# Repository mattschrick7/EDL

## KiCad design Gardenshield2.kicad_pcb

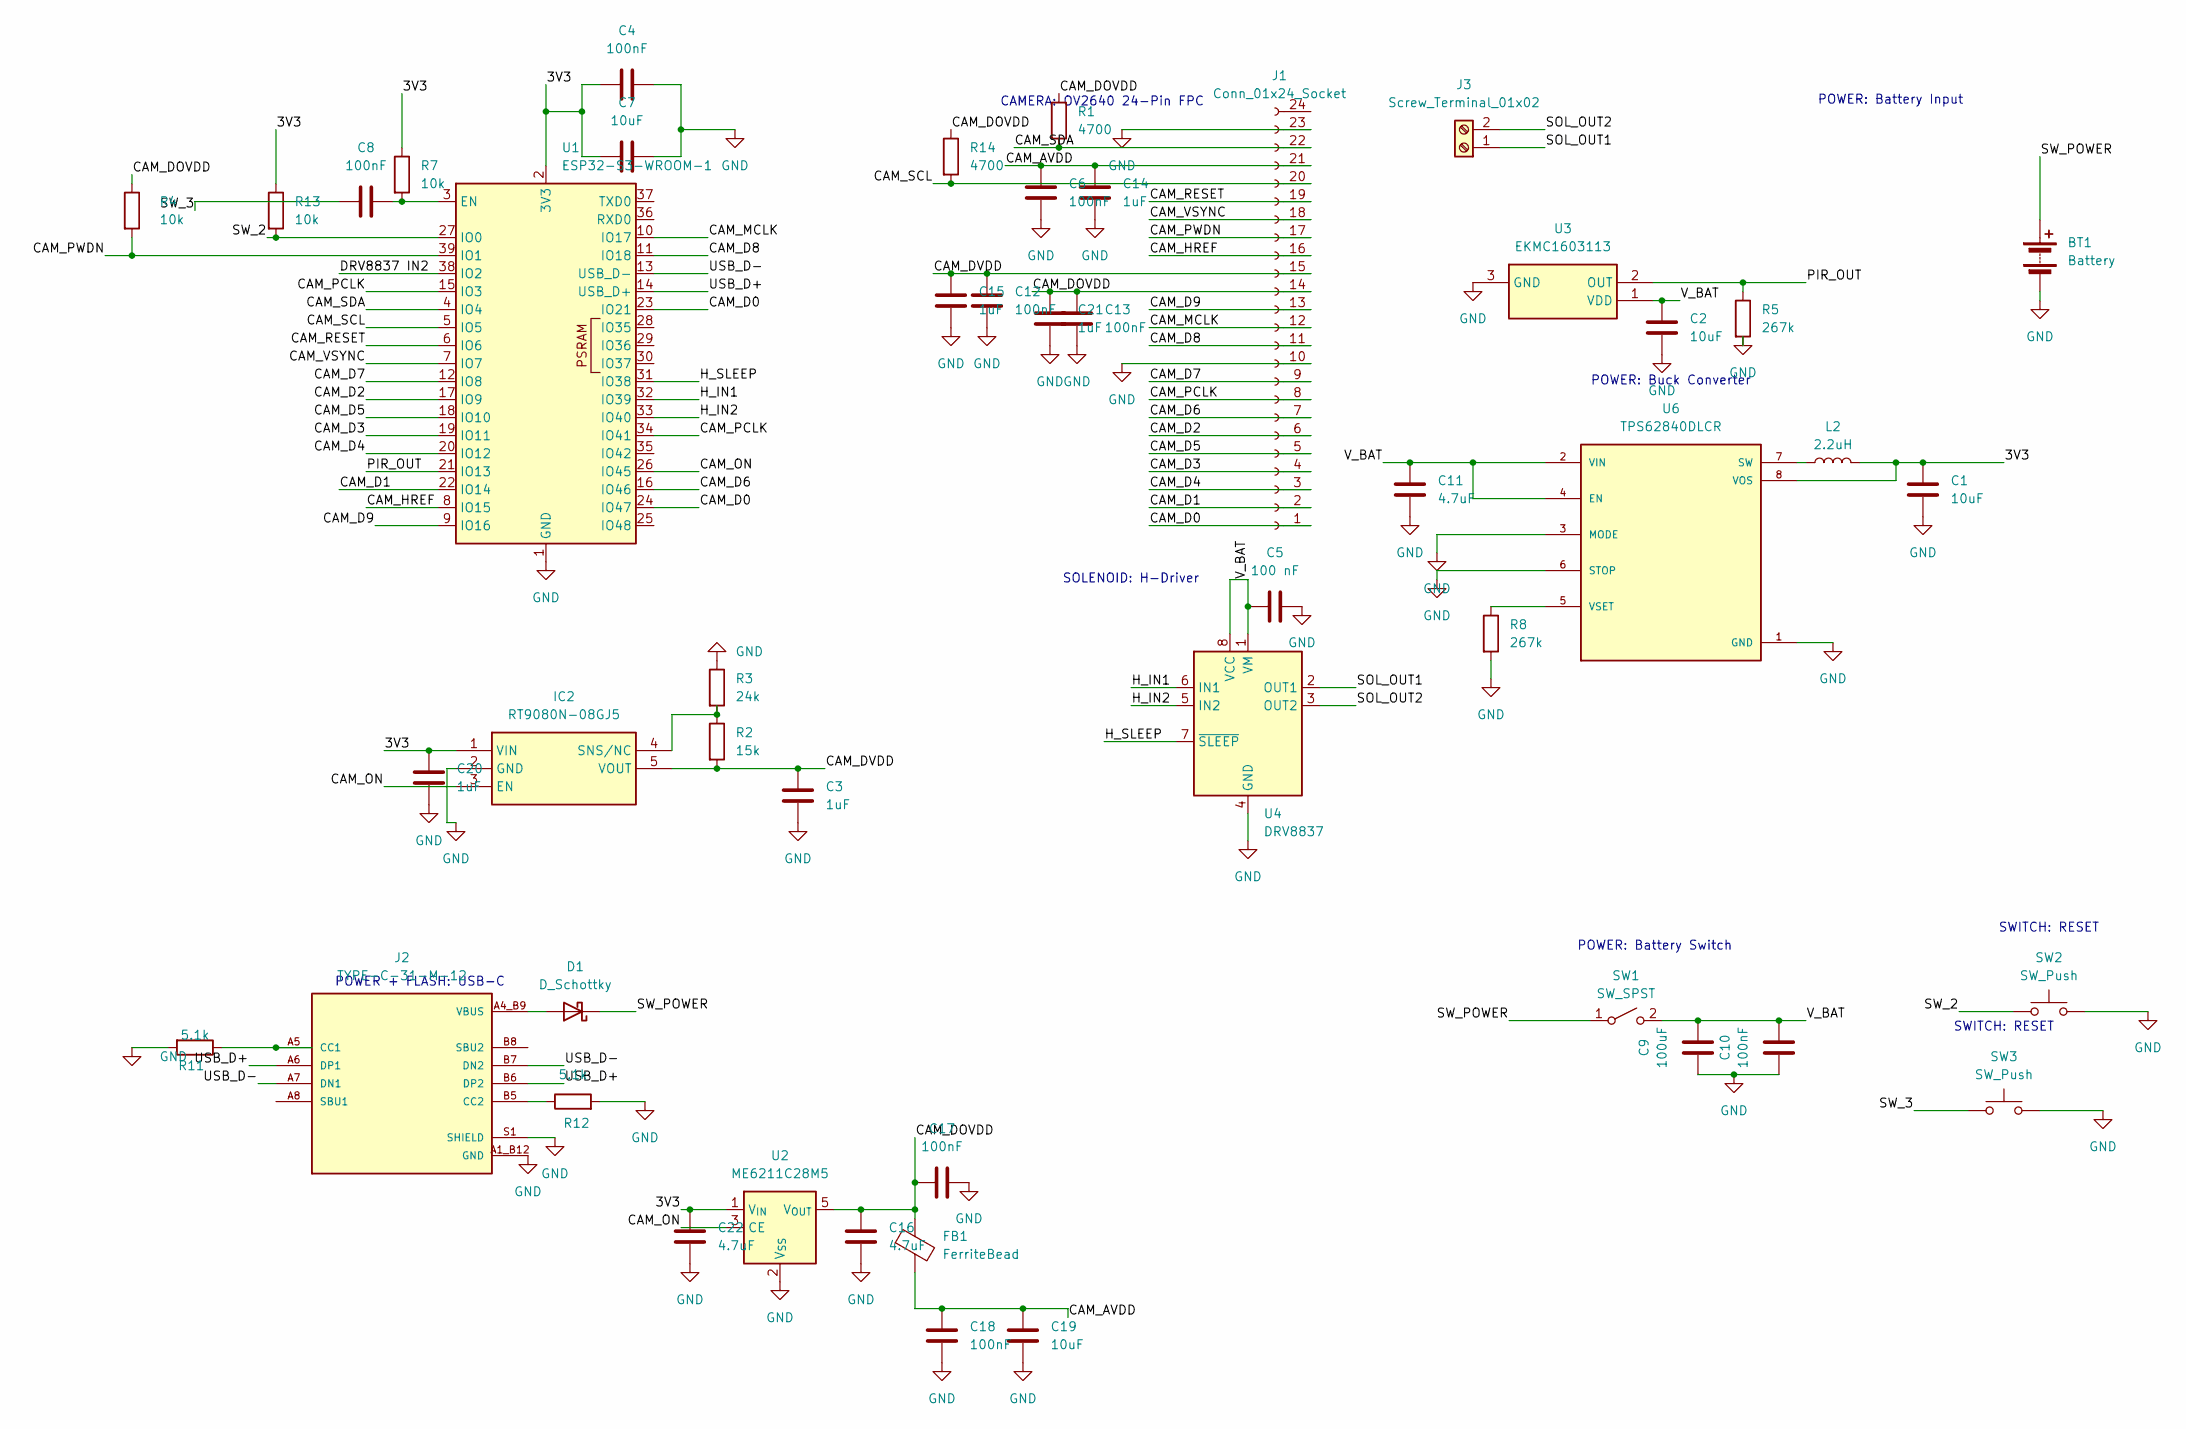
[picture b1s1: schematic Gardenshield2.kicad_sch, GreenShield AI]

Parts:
BT1: Battery; BatteryHolder_TruPower_BH-331P_3xAA
C1, C2, C7, C19: 10uF; C_0805_2012Metric
C3: 1uF; C_0402_1005Metric
C4, C6, C8, C10, C12, C13, C17, C18: 100nF; C_0603_1608Metric
C5: 100 nF; C_0603_1608Metric
C9: 100uF; CP_Elec_6.3x5.8
C11, C16, C22: 4.7uF; C_0603_1608Metric
C14, C15, C20, C21: 1uF; C_0603_1608Metric
D1: D_Schottky; D_SMA
FB1: FerriteBead; C_0805_2012Metric
IC2: RT9080N-08GJ5; SOT94P280X100-5N; Mouser Part Number 835-RT9080N-08GJ5
J1: Conn_01x24_Socket; F32R1A7H111024
J2: TYPE-C-31-M-12; HRO_TYPE-C-31-M-12; PARTREV 2020.12.08
J3: Screw_Terminal_01x02; TerminalBlock_MaiXu_MX126-5.0-02P_1x02_P5.00mm
L2: 2.2uH; L_0805_2012Metric
R1, R14: 4700; R_0603_1608Metric
R2: 15k; R_0805_2012Metric
R3: 24k; R_0805_2012Metric
R4, R7, R13: 10k; R_0603_1608Metric
R5, R8: 267k; R_0603_1608Metric
R11, R12: 5.1k; R_0603_1608Metric
SW1: SW_SPST; SW_TS-1088-AR02016
SW2, SW3: SW_Push; SW_TS-1088-AR02016
U1: ESP32-S3-WROOM-1
U2: ME6211C28M5; SOT-23-5
U3: EKMC1603113; Mouser Part Number 769-EKMC1603113
U4: DRV8837; WSON-8-1EP_2x2mm_P0.5mm_EP0.9x1.6mm
U6: TPS62840DLCR; SON50P200X150X100-8N

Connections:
/3V3: C1.1, C4.1, C7.1, C20.1, C22.1, IC2.1 (VIN), L2.2, R7.1, R13.1, U1.2 (3V3), U2.1 (V_{IN}), U6.8 (VOS)
/CAM_AVDD: C6.1, C14.1, C18.1, C19.1, FB1.2, J1.21
/CAM_D0: J1.1, U1.23 (IO21), U1.24 (IO47)
/CAM_D1: J1.2, U1.22 (IO14)
/CAM_D2: J1.6, U1.17 (IO9)
/CAM_D3: J1.4, U1.19 (IO11)
/CAM_D4: J1.3, U1.20 (IO12)
/CAM_D5: J1.5, U1.18 (IO10)
/CAM_D6: J1.7, U1.16 (IO46)
/CAM_D7: J1.9, U1.12 (IO8)
/CAM_D8: J1.11, U1.11 (IO18)
/CAM_D9: J1.13, U1.9 (IO16)
/CAM_DOVDD: C13.1, C16.1, C17.1, C21.1, FB1.1, J1.14, R1.1, R4.1, R14.1, U2.5 (V_{OUT})
/CAM_DVDD: C3.1, C12.1, C15.1, IC2.5 (VOUT), J1.15, R2.2
/CAM_HREF: J1.16, U1.8 (IO15)
/CAM_MCLK: J1.12, U1.10 (IO17)
/CAM_ON: IC2.3 (EN), U1.26 (IO45), U2.3 (CE)
/CAM_PCLK: J1.8, U1.15 (IO3), U1.34 (IO41)
/CAM_PWDN: J1.17, R4.2, U1.39 (IO1)
/CAM_RESET: J1.19, U1.6 (IO6)
/CAM_SCL: J1.20, R14.2, U1.5 (IO5)
/CAM_SDA: J1.22, R1.2, U1.4 (IO4)
/CAM_VSYNC: J1.18, U1.7 (IO7)
/DRV8837 IN2: U1.38 (IO2)
/H_IN1: U1.32 (IO39), U4.6 (IN1)
/H_IN2: U1.33 (IO40), U4.5 (IN2)
/H_SLEEP: U1.31 (IO38), U4.7 (~SLEEP)
/PIR_OUT: R5.1, U1.21 (IO13), U3.2 (OUT)
/SOL_OUT1: J3.1, U4.2 (OUT1)
/SOL_OUT2: J3.2, U4.3 (OUT2)
/SW_2: R13.2, SW2.1, U1.27 (IO0)
/SW_3: C8.1, SW3.1
/SW_POWER: BT1.1 (+), D1.1 (K), SW1.1 (A)
/USB_D+: J2.A6 (DP1), J2.B6 (DP2), U1.14 (USB_D+)
/USB_D-: J2.A7 (DN1), J2.B7 (DN2), U1.13 (USB_D-)
/V_BAT: C2.1, C5.1, C9.2, C10.2, C11.1, SW1.2 (B), U3.1 (VDD), U4.1 (VM), U4.8 (VCC), U6.2 (VIN), U6.4 (EN)
GND: BT1.2 (-), C1.2, C2.2, C3.2, C4.2, C5.2, C6.2, C7.2, C9.1, C10.1, C11.2, C12.2, C13.2, C14.2, C15.2, C16.2, C17.2, C18.2, C19.2, C20.2, C21.2, C22.2, IC2.2 (GND), J1.10, J1.23, J2.A1_B12 (GND), J2.B1_A12 (GND), J2.S1 (SHIELD), J2.S2 (SHIELD), J2.S3 (SHIELD), J2.S4 (SHIELD), R3.1, R5.2, R8.2, R11.2, R12.2, SW2.2, SW3.2, U1.1 (GND), U1.40 (GND), U1.41 (GND), U2.2 (V_{SS}), U3.3 (GND), U4.4 (GND), U4.9 (GND), U6.1 (GND), U6.3 (MODE), U6.6 (STOP)
unnamed: IC2.4 (SNS/NC), R2.1, R3.2
unnamed: J2.A5 (CC1), R11.1
unnamed: J2.B5 (CC2), R12.1
unnamed: C8.2, R7.2, U1.3 (EN)
unnamed: L2.1, U6.7 (SW)
unnamed: R8.1, U6.5 (VSET)
VBUS: D1.2 (A), J2.A4_B9 (VBUS), J2.B4_A9 (VBUS)

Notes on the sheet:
POWER: Battery Switch
SWITCH: RESET
POWER + FLASH: USB-C
POWER: Buck Converter
SOLENOID: H-Driver
POWER: Battery Input
CAMERA: OV2640 24-Pin FPC

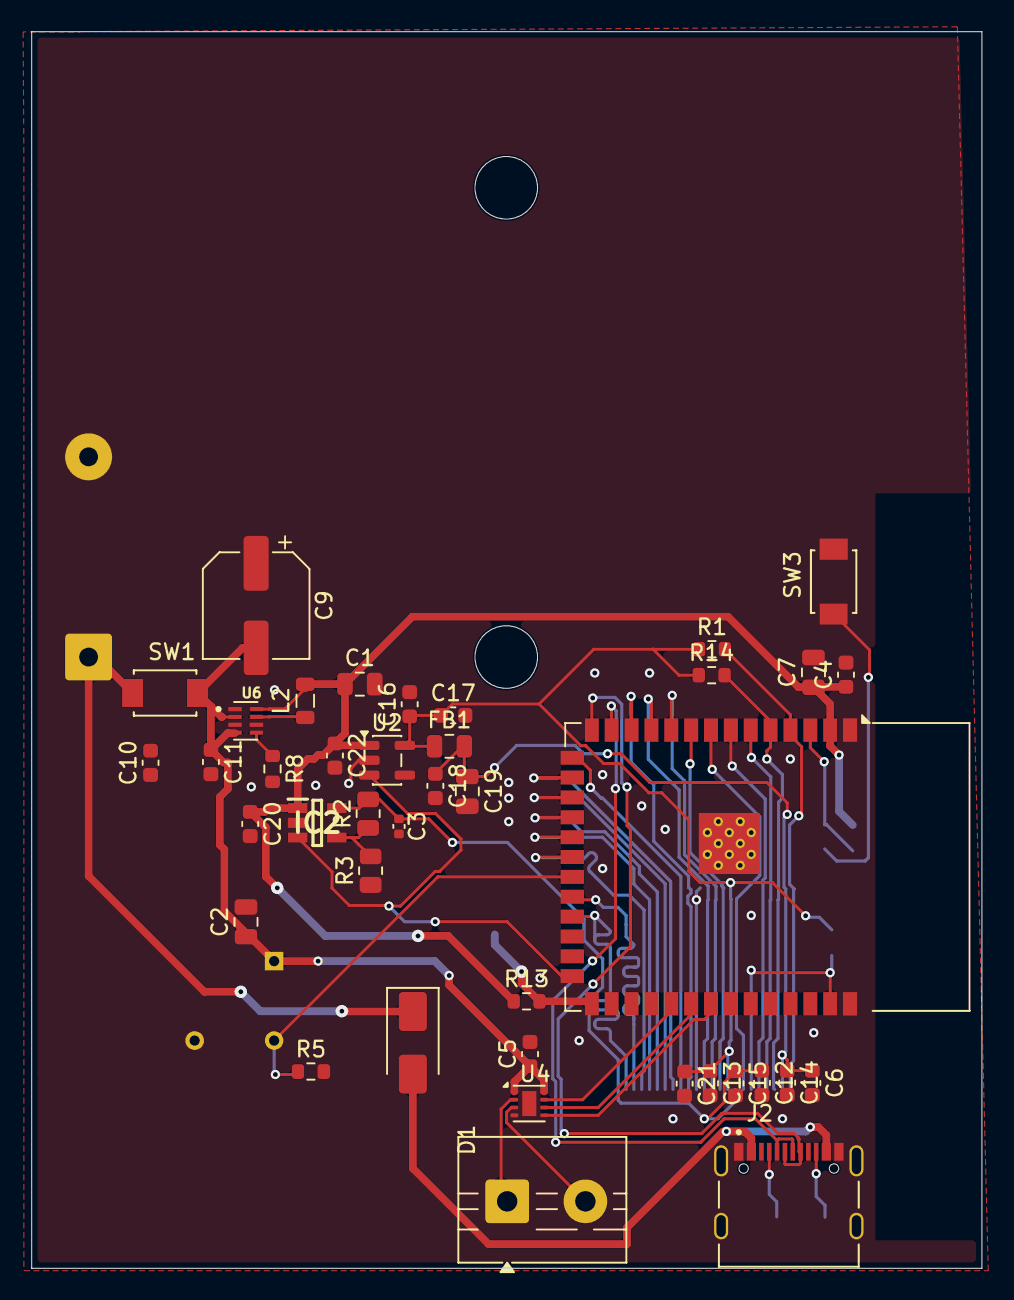
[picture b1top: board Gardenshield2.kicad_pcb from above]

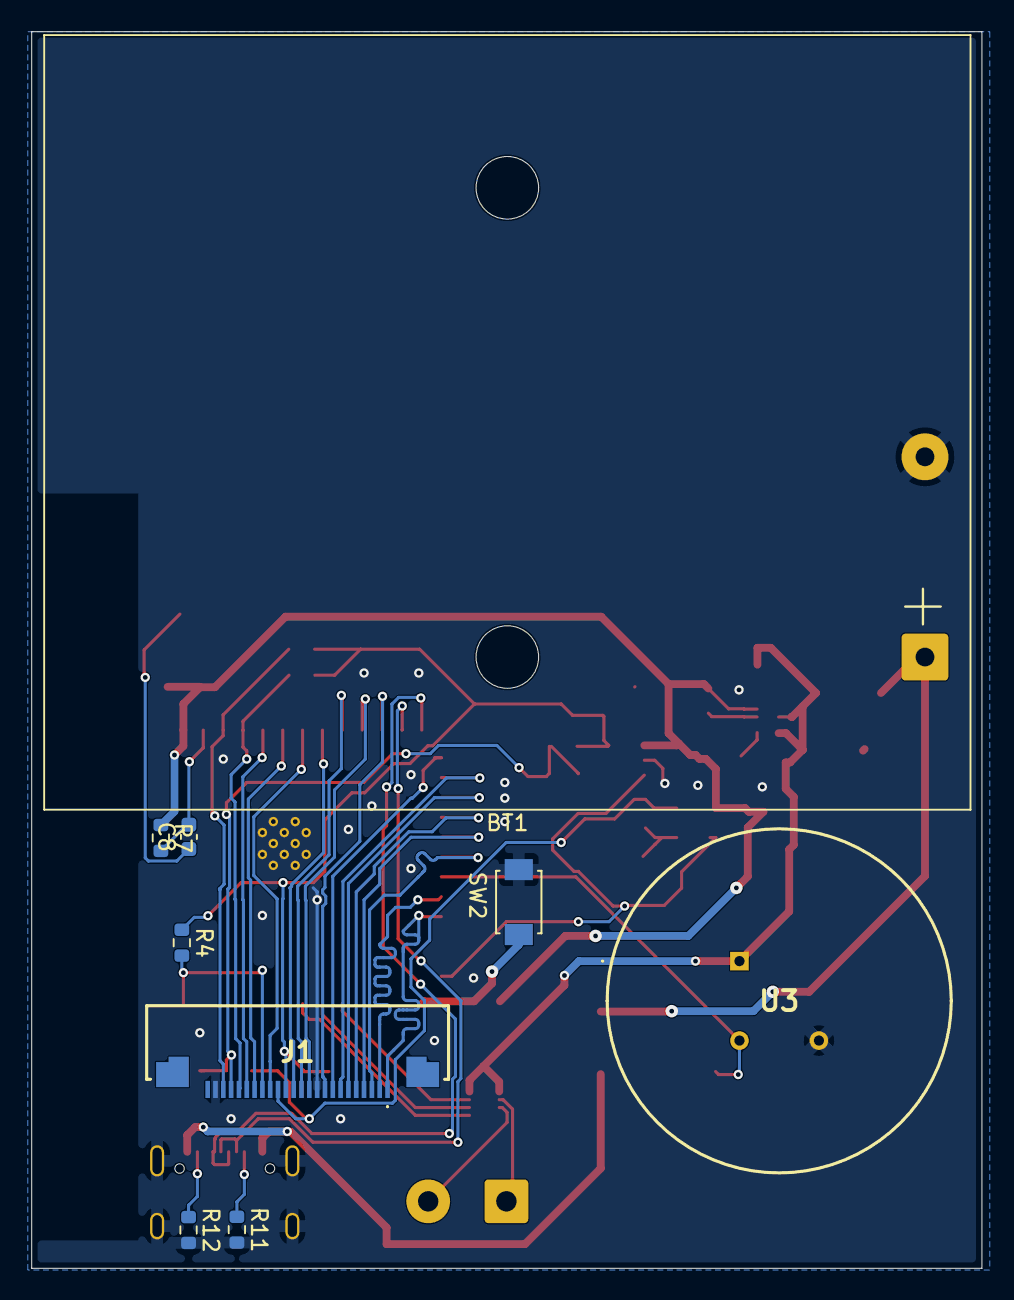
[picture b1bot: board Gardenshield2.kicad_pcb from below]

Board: 4 copper layers, 60.8 x 79.1 mm, 49 parts (9 on the bottom side), 43 nets.
